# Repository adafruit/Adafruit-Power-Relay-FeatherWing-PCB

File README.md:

## Adafruit Power Relay FeatherWing PCB
<a href="http://www.adafruit.com/products/3191"><br/>
Click here to purchase one from the Adafruit shop</a>

This is the Power Relay FeatherWing. It gives you power to control, and control over power. Put simply, you can now turn on and off lamps, fans, solenoids, and other small appliances that run on up to 250VAC or DC power using any Feather board. Compared to our smaller Relay FeatherWings, this one can handle a beefy 1200 Watts!

Works with all/any of our Feather boards, just wire up the relay control pin to whatever GPIO you like! Using our Feather Stacking Headers or Feather Female Headers you can connect a FeatherWing on top of your Feather board and let the board take flight. Check out our range of Feather boards here.

This Wing has a non-latching type relay. You can switch up to 10A of resistive-load current at 120VAC, 5A at 240VAC. With inductive loads, about half that. Check the datasheet for the relay for the exact switching capacity, as it depends on type of load and voltage type and magnitude. This relay is good for handling fairly large devices, computers, TVs, small appliances and more.

PCB files for the Adafruit Power Relay FeatherWing. The format is EagleCAD schematic and board layout
- https://www.adafruit.com/products/3191

### License

Adafruit invests time and resources providing this open source design, please support Adafruit and open-source hardware by purchasing products from [Adafruit](https://www.adafruit.com)!

All text above must be included in any redistribution

Designed by Limor Fried/Ladyada for Adafruit Industries.
Creative Commons Attribution/Share-Alike, all text above must be included in any redistribution. 
See license.txt for additional information.

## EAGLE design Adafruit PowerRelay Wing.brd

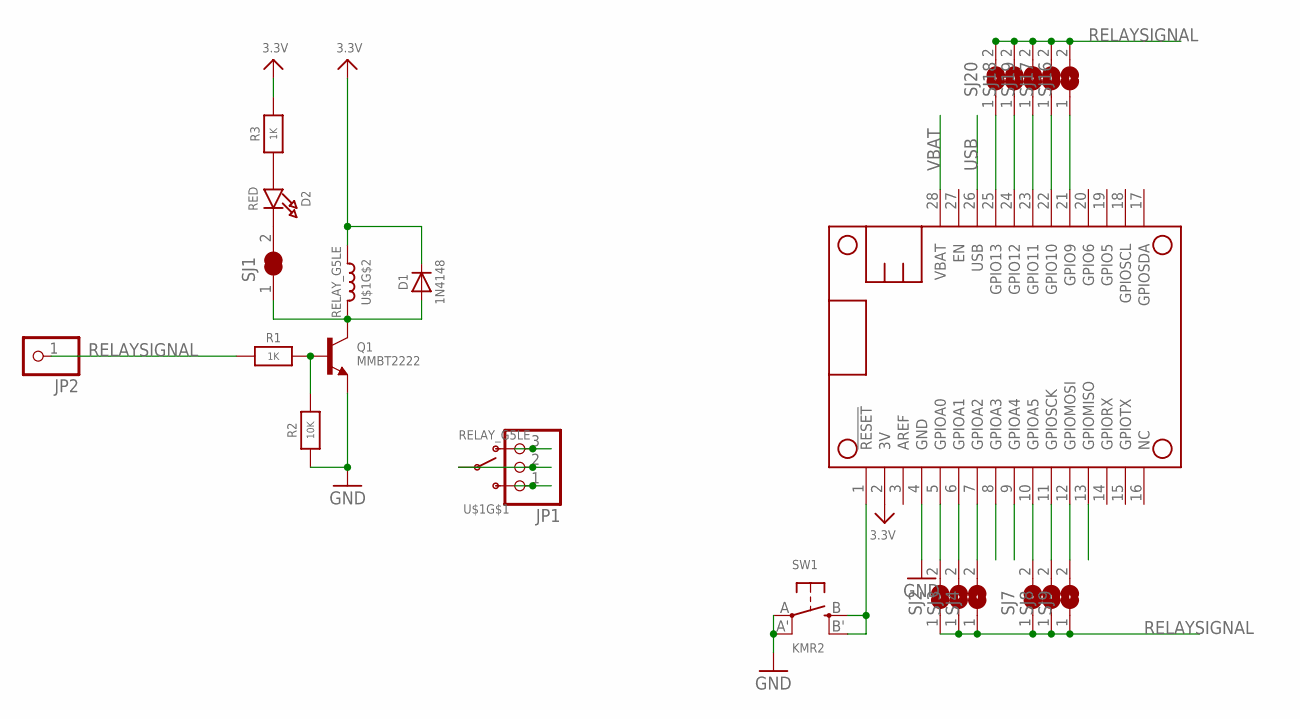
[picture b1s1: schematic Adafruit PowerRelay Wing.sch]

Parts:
D1: 1N4148; SOD-323
D2: RED; CHIPLED_0805_NOOUTLINE
JP1: HEADER-1X3_508TERM; TERMBLOCK_1X3_5.08MM
JP2: HEADER-1X1ROUND; 1X01_ROUND
MS2: FEATHERWING
Q1: MMBT2222; SOT23-R
R1, R3: 1K; 0805-NO
R2: 10K; 0805-NO
SJ1: SOLDERJUMPER_CLOSED; SOLDERJUMPER_CLOSEDWIRE
SJ2, SJ3, SJ4, SJ7, SJ8, SJ9, SJ16, SJ17, SJ18, SJ19, SJ20: SOLDERJUMPER; SOLDERJUMPER_ARROW_NOPASTE
SW1: KMR2; BTN_KMR2_4.6X2.8
U$1: RELAY_G5LE; RELAY_G5LE-1

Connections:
3.3V: D1.C, MS2.2 (3V), R3.2, U$1.2 (1)
GND: MS2.4 (GND), Q1.2 (E), R2.1, SW1.A, SW1.A' (P1)
unnamed: JP1.2, U$1.1
unnamed: JP1.3, U$1.3 (O)
unnamed: JP1.1, U$1.4 (S)
unnamed: D1.A, Q1.3 (C), SJ1.1, U$1.5 (2)
unnamed: MS2.12 (GPIOMOSI), SJ9.2
unnamed: MS2.11 (GPIOSCK), SJ8.2
unnamed: MS2.10 (GPIOA5), SJ7.2
unnamed: MS2.7 (GPIOA2), SJ4.2
unnamed: MS2.6 (GPIOA1), SJ3.2
unnamed: MS2.5 (GPIOA0), SJ2.2
unnamed: MS2.25 (GPIO13), SJ20.1
unnamed: MS2.24 (GPIO12), SJ18.1
unnamed: MS2.1 (!RESET), SW1.B (S), SW1.B' (S1)
unnamed: MS2.23 (GPIO11), SJ19.1
unnamed: MS2.22 (GPIO10), SJ17.1
unnamed: MS2.21 (GPIO9), SJ16.1
unnamed: Q1.1 (B), R1.2, R2.2
unnamed: D2.C, SJ1.2
unnamed: D2.A, R3.1
RELAYSIGNAL: JP2.1, R1.1, SJ2.1, SJ3.1, SJ4.1, SJ7.1, SJ8.1, SJ9.1, SJ16.2, SJ17.2, SJ18.2, SJ19.2, SJ20.2
USB: MS2.26 (USB)
VBAT: MS2.28 (VBAT)

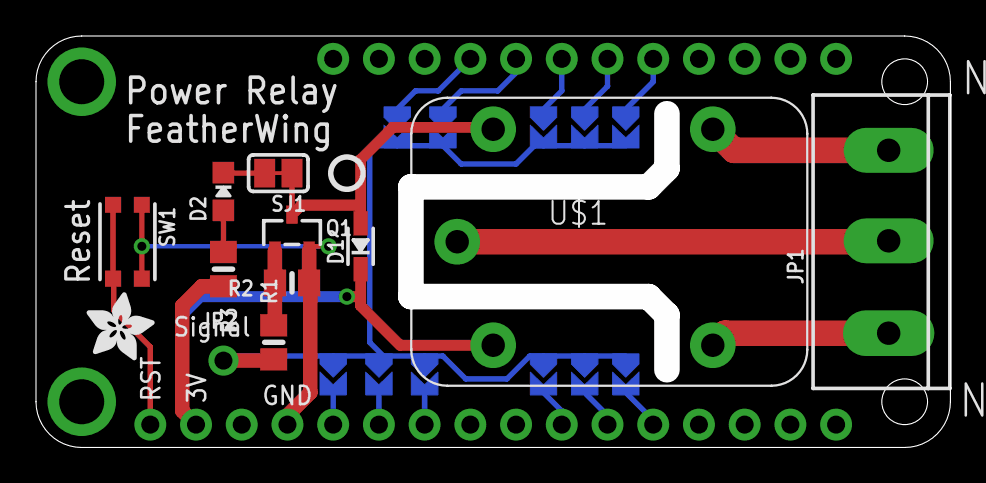
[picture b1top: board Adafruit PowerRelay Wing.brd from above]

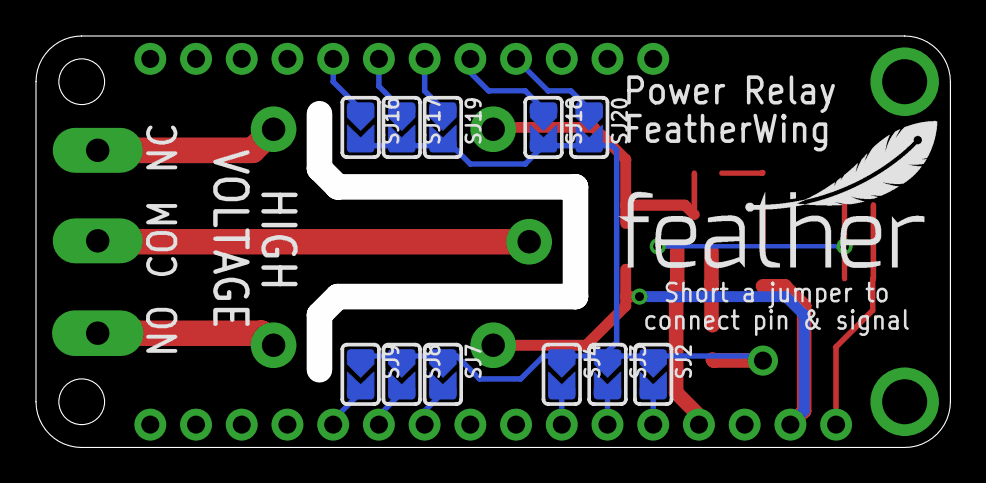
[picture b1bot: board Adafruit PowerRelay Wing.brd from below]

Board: 2 copper layers, 49.4 x 21.4 mm, 26 parts (12 on the bottom side), 22 nets.

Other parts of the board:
U$5: PCBFEAT-REV-040
U$6: ADAFRUIT_3.5MM
U$7: FEATHERLOGO_MED

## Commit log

2016-08-17 init

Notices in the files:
parts and their libraries:
microbuilder: This work is placed in the public domain, and may be freely used for commercial and non-commercial work with the following conditions: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
